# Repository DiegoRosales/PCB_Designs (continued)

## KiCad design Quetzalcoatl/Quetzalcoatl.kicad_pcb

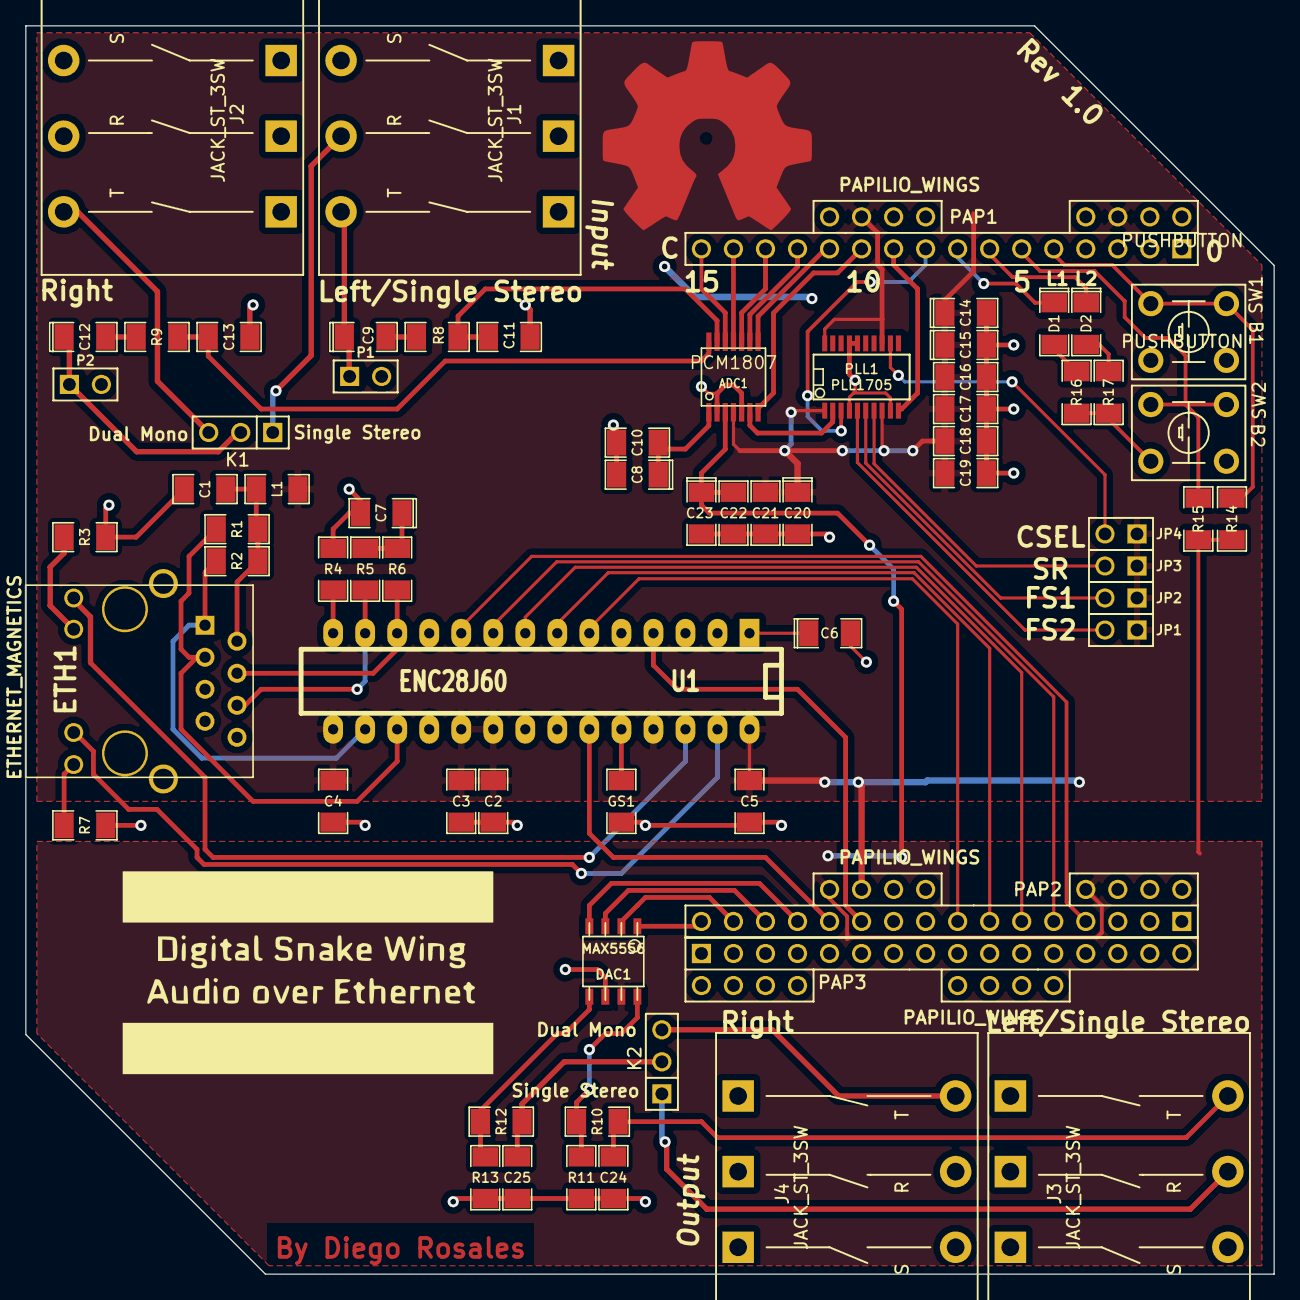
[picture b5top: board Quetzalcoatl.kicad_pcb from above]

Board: 2 copper layers, 99.0 x 99.0 mm, 68 parts (0 on the bottom side), 61 nets.

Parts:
ADC1: PCM1807; tssop-14
C1: 100nF; SM1206
C2, C3, C4, C5: 180nF; SM1206
C6, C8, C14, C15, C20, C23: 10uF; SM1206POL
C7: 10nF; SM1206POL
C9, C12: 1uF; SM1206POL
C10, C16, C17, C18, C19, C21, C22: 0.1uF; SM1206
C11, C13: 80nF; SM1206
C24, C25: 1.5nF; SM1206
D1, D2: LED; SM1206POL
DAC1: MAX5556; so-8
ETH1: ETHERNET_MAGNETICS; PRT-08534
GS1: GS2; SM1206
J1, J2, J3, J4: JACK_ST_3SW; Jack_6.35_Stereo_SW
JP1, JP2, JP3, JP4: JUMPER; PIN_ARRAY_2X1
K1, K2: CONN_3; PIN_ARRAY_3X1
L1: FERRITE_BEAD; SM1206
P1, P2: CONN_2; PIN_ARRAY_2X1
PAP1, PAP2, PAP3: PAPILIO_WINGS; Papilio_Wing
PLL1: PLL1705; SSOP20
R1, R2, R5, R6: 49.9, 1%; SM1206
R3, R7: 180R; SM1206
R4: 2.32k, 1%; SM1206
R8, R9: 100R; SM1206
R10, R12: 560R; SM1206
R11, R13: 100k; SM1206
R14, R15, R16, R17: 1k; SM1206
SW1, SW2: PUSHBUTTON; TactileSW_2
U1: ENC28J60; DIP-28__300_ELL

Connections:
+3.3V: ADC1.4, C2.1, C3.1, C4.1, C5.1, C14.1, C15.1, C16.1, C17.1, C18.1, C19.1, C20.1, C21.1, JP1.1, JP2.1, JP3.1, JP4.1, L1.1, PAP1.18, PAP1.22, PAP2.18, PLL1.1, PLL1.8, PLL1.13, PLL1.20, U1.15, U1.19, U1.20, U1.25, U1.28
+5V: ADC1.3, C22.1, C23.1, DAC1.7, PAP2.17, PAP2.21, R14.2, R15.2
/ADC/384fs: PAP1.9, PLL1.3
/ADC/ADC_CTRL_CK: ADC1.11, PAP1.15
/ADC/ADC_CTRL_DATA: ADC1.10, PAP1.14
/ADC/ADC_CTRL_SEL: ADC1.12, PAP1.16
/ADC/BCK: ADC1.8, PAP1.12
/ADC/CK27: PAP1.10, PLL1.10
/ADC/D_ADC: ADC1.9, PAP1.13
/ADC/LRCK: ADC1.7, PAP1.11
/ADC/Vin_L: ADC1.13, C11.1, R8.2
/ADC/Vin_R: ADC1.14, C13.1, R9.2
/DAC/LRCLK: DAC1.3, PAP2.14
/DAC/MCLK: DAC1.4, PAP2.13
/DAC/SCLK: DAC1.2, PAP2.15
/DAC/SDATA: DAC1.1, PAP2.16
/Ethernet/CK25: PAP2.12, U1.23
/Ethernet/CS: PAP2.5, U1.9
/Ethernet/ETH_INT: PAP2.11, U1.4
/Ethernet/LED_A: ETH1.11, U1.27
/Ethernet/LED_B: ETH1.9, U1.26
/Ethernet/MISO: PAP2.8, U1.6
/Ethernet/MOSI: PAP2.7, U1.7
/Ethernet/RESET: PAP2.4, U1.10
/Ethernet/SCK: PAP2.6, U1.8
/Misc/LED1: D1.1, PAP1.8
/Misc/LED2: D2.1, PAP1.7
/Misc/PB1: PAP1.5, R14.1, SW1.1, SW1.2
/Misc/PB2: PAP1.6, R15.1, SW2.1, SW2.2
GND: ADC1.2, ADC1.5, C1.2, C2.2, C3.2, C4.2, C5.2, C6.2, C7.2, C8.2, C10.2, C11.2, C13.2, C14.2, C15.2, C16.2, C17.2, C18.2, C19.2, C20.2, C21.2, C22.2, C23.2, C24.2, C25.2, DAC1.6, ETH1.8, GS1.2, J1.1, J1.3, J1.5, J1.6, J2.1, J2.3, J2.5, J2.6, J3.1, J3.3, J3.5, J3.6, J4.1, J4.3, J4.5, J4.6, P1.2, P2.2, PAP1.20, PAP1.24, PAP2.20, PAP2.24, PLL1.4, PLL1.9, PLL1.16, PLL1.17, R3.2, R4.1, R7.2, R11.1, R13.1, R16.2, R17.2, SW1.3, SW1.4, SW2.3, SW2.4, U1.2, U1.11, U1.18, U1.21, U1.22
unnamed: ETH1.10, R3.1
unnamed: ETH1.12, R7.1
unnamed: C7.1, R5.2, R6.2
unnamed: ETH1.6, R5.1, U1.13
unnamed: ETH1.1, R2.2, U1.16
unnamed: ETH1.3, R1.2, U1.17
unnamed: C6.1, U1.1
unnamed: R4.2, U1.14
unnamed: GS1.1, U1.24
unnamed: ETH1.4, R6.1, U1.12
unnamed: C1.1, ETH1.2, L1.2, R1.1, R2.1
unnamed: C9.1, J1.2, P1.1
unnamed: J1.4, K1.1
unnamed: J2.2, K1.3
unnamed: C12.1, K1.2, P2.1
unnamed: JP2.2, PLL1.6
unnamed: JP4.2, PLL1.12
unnamed: ADC1.1, C8.1, C10.1
unnamed: C9.2, R8.1
unnamed: C12.2, R9.1
unnamed: ADC1.6, PLL1.2
unnamed: JP1.2, PLL1.5
unnamed: JP3.2, PLL1.7
unnamed: J4.2, K2.3
unnamed: DAC1.8, R10.1, R11.2
unnamed: DAC1.5, R12.1, R13.2
unnamed: J3.4, K2.1
unnamed: C25.1, K2.2, R12.2
unnamed: C24.1, J3.2, R10.2
unnamed: D2.2, R17.1
unnamed: D1.2, R16.1

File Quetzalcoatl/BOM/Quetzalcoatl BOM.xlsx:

| Ref | Value | Qty per board | Total Qty | Part No. | Distributor | Dist. No. | Unit price (USD) | Cost
 | ADC1 | PCM1807 | 1 | 2 | PCM1807 | - | - | 0 | 0 |  | Boards | 2
 | C1 | 100nF | 1 | 2 | MC1206B104J500CT | Newark | 90W2887 | 0.29199999999999998 | 0.58399999999999996 |  | Total | 8.088000000000001
 | C10, C16, C17, C18, C19, C21, C22 | 0.1uF | 7 | 14 | CC1206KRX7R9BB104 | Newark | 68R4967 | 3.6999999999999998E-2 | 0.51800000000000002 |  | Total per board | 4.0440000000000005
 | C11, C13 | 80nF | 2 | 4 | C1206C183K5RACTU | Newark | 70K9301 | 4.9000000000000002E-2 | 0.19600000000000001
 | C2, C3, C4, C5 | 180nF | 4 | 8 | MC1206B184K250CT | Newark | 33R0653 | 7.2999999999999995E-2 | 0.58399999999999996
 | C24, C25 | 1.5nF | 2 | 4 | MC1206B152K102CT | Newark | 21T9895 | 0.03 | 0.12
 | C6, C8, C14, C15, C20, C23 | 10uF | 6 | 12 | 100R18Y106ZV4E | Newark | 82H2447 | 0.06 | 0.72
 | C7 | 10nF | 1 | 2 | 12061C103JAT2A | Newark | 96M1464 | 6.0999999999999999E-2 | 0.122
 | C9, C12 | 1uF | 2 | 4 | CC1206KKX7R7BB105 | Newark | 68R4957 | 0.06 | 0.24
 | DAC1 | MAX5556 | 1 | 2 | MAX5556 | - | - | 0 | 0
 | ETH1 | ETHERNET_MAGNETICS | 1 | 2 | PRT-08534 | Sparkfun |  | 1.95 | 3.9
 | GS1 | GS2 | 1 | 2 | - | - | - | 0 | 0
 | J1, J2, J3, J4 | JACK_ST_3SW | 4 | 8 | - | - | - | 0 | 0
 | JP1, JP2, JP3, JP4 | JUMPER | 4 | 8 | - | - | - | 0 | 0
 | L1 | FERRITE_BEAD | 1 | 2 | 2512061217Y0 | Newark | 32C8661 | 3.1E-2 | 6.2E-2
 | P1, P2 | CONN_2 | 2 | 4 | - | - | - | 0 | 0
 | PAP1, PAP2 | PAPILIO_WINGS | 2 | 4 | - | - | - | 0 | 0
 | PLL1 | PLL1705 | 1 | 2 | PLL1705 | - | - | 0 | 0
 | R1, R2, R5, R6 | 49.9R, 1% | 4 | 8 | CR1206-FX-49R9ELF | Newark | 02J2615 | 0.10100000000000001 | 0.80800000000000005
 | R10, R12 | 560R | 2 | 4 | CRCW1206560RFKEA | Newark | 42K5124 | 8.9999999999999993E-3 | 3.5999999999999997E-2
 | R11, R13 | 100k | 2 | 4 | MC0125W12061100K | Newark | 39K0873 | 2.1999999999999999E-2 | 8.7999999999999995E-2
 | R3, R7 | 180R | 2 | 4 | WCR1206-180RFI | Newark | 98K2692 | 1.0999999999999999E-2 | 4.3999999999999997E-2
 | R4 | 2.32k, 1% | 1 | 2 | CRCW12062K32FKEA | Newark | 53K2064 | 8.9999999999999993E-3 | 1.7999999999999999E-2
 | R8, R9 | 100R | 2 | 4 | MC0125W12065100R | Newark | 39K0992 | 1.2E-2 | 4.8000000000000001E-2
 | U1 | ENC28J60 | 1 | 2 | ENC28J60 | - | - | 0 | 0

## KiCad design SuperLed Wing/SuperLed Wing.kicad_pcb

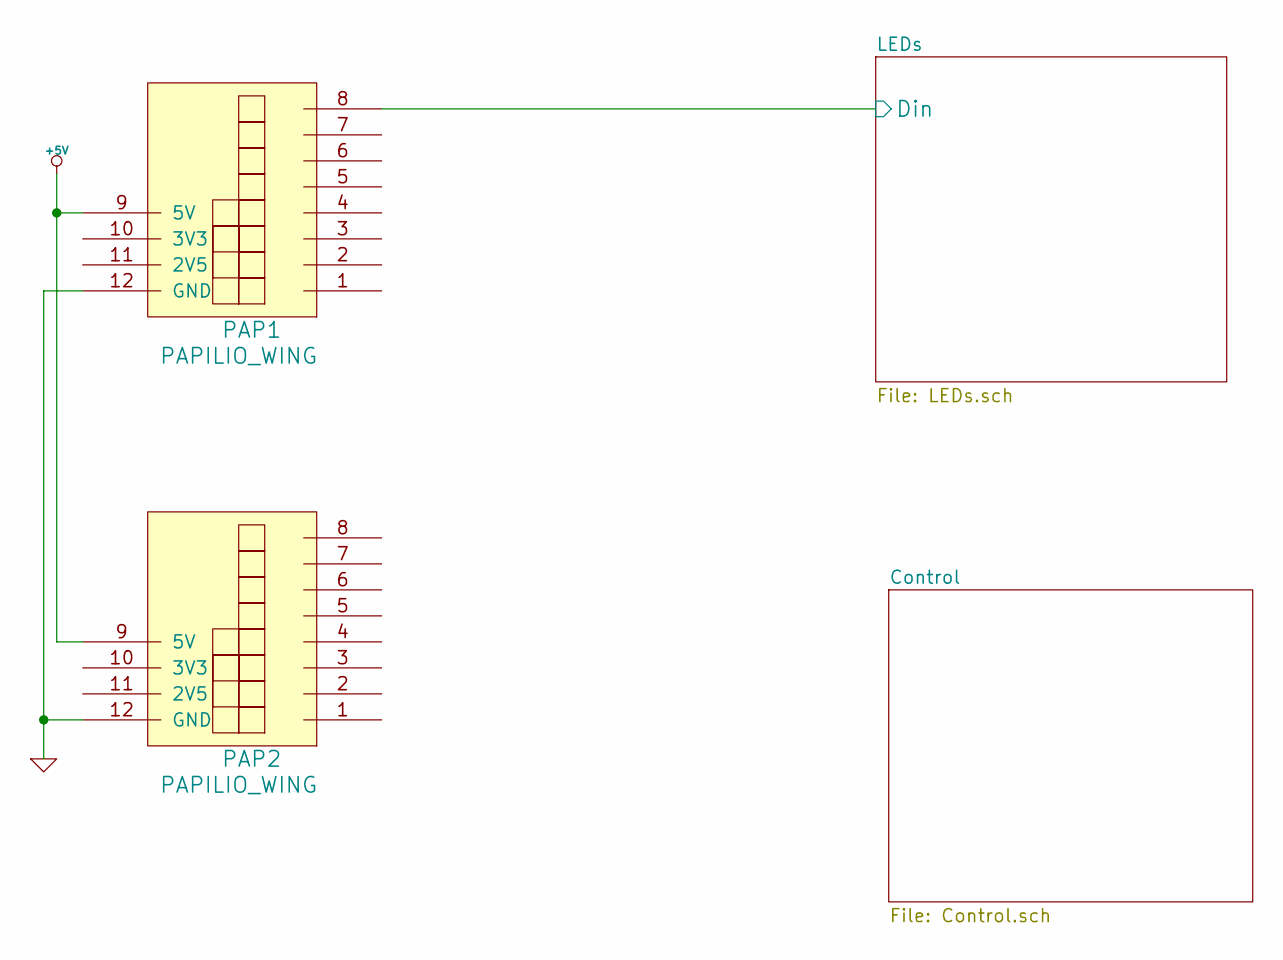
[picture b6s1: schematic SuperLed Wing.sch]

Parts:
PAP1, PAP2: PAPILIO_WING

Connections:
+5V: PAP1.9 (5V), PAP2.9 (5V)
/LEDs/Din: PAP1.8; also elsewhere on the board
GND: PAP1.12 (GND), PAP2.12 (GND); also elsewhere on the board

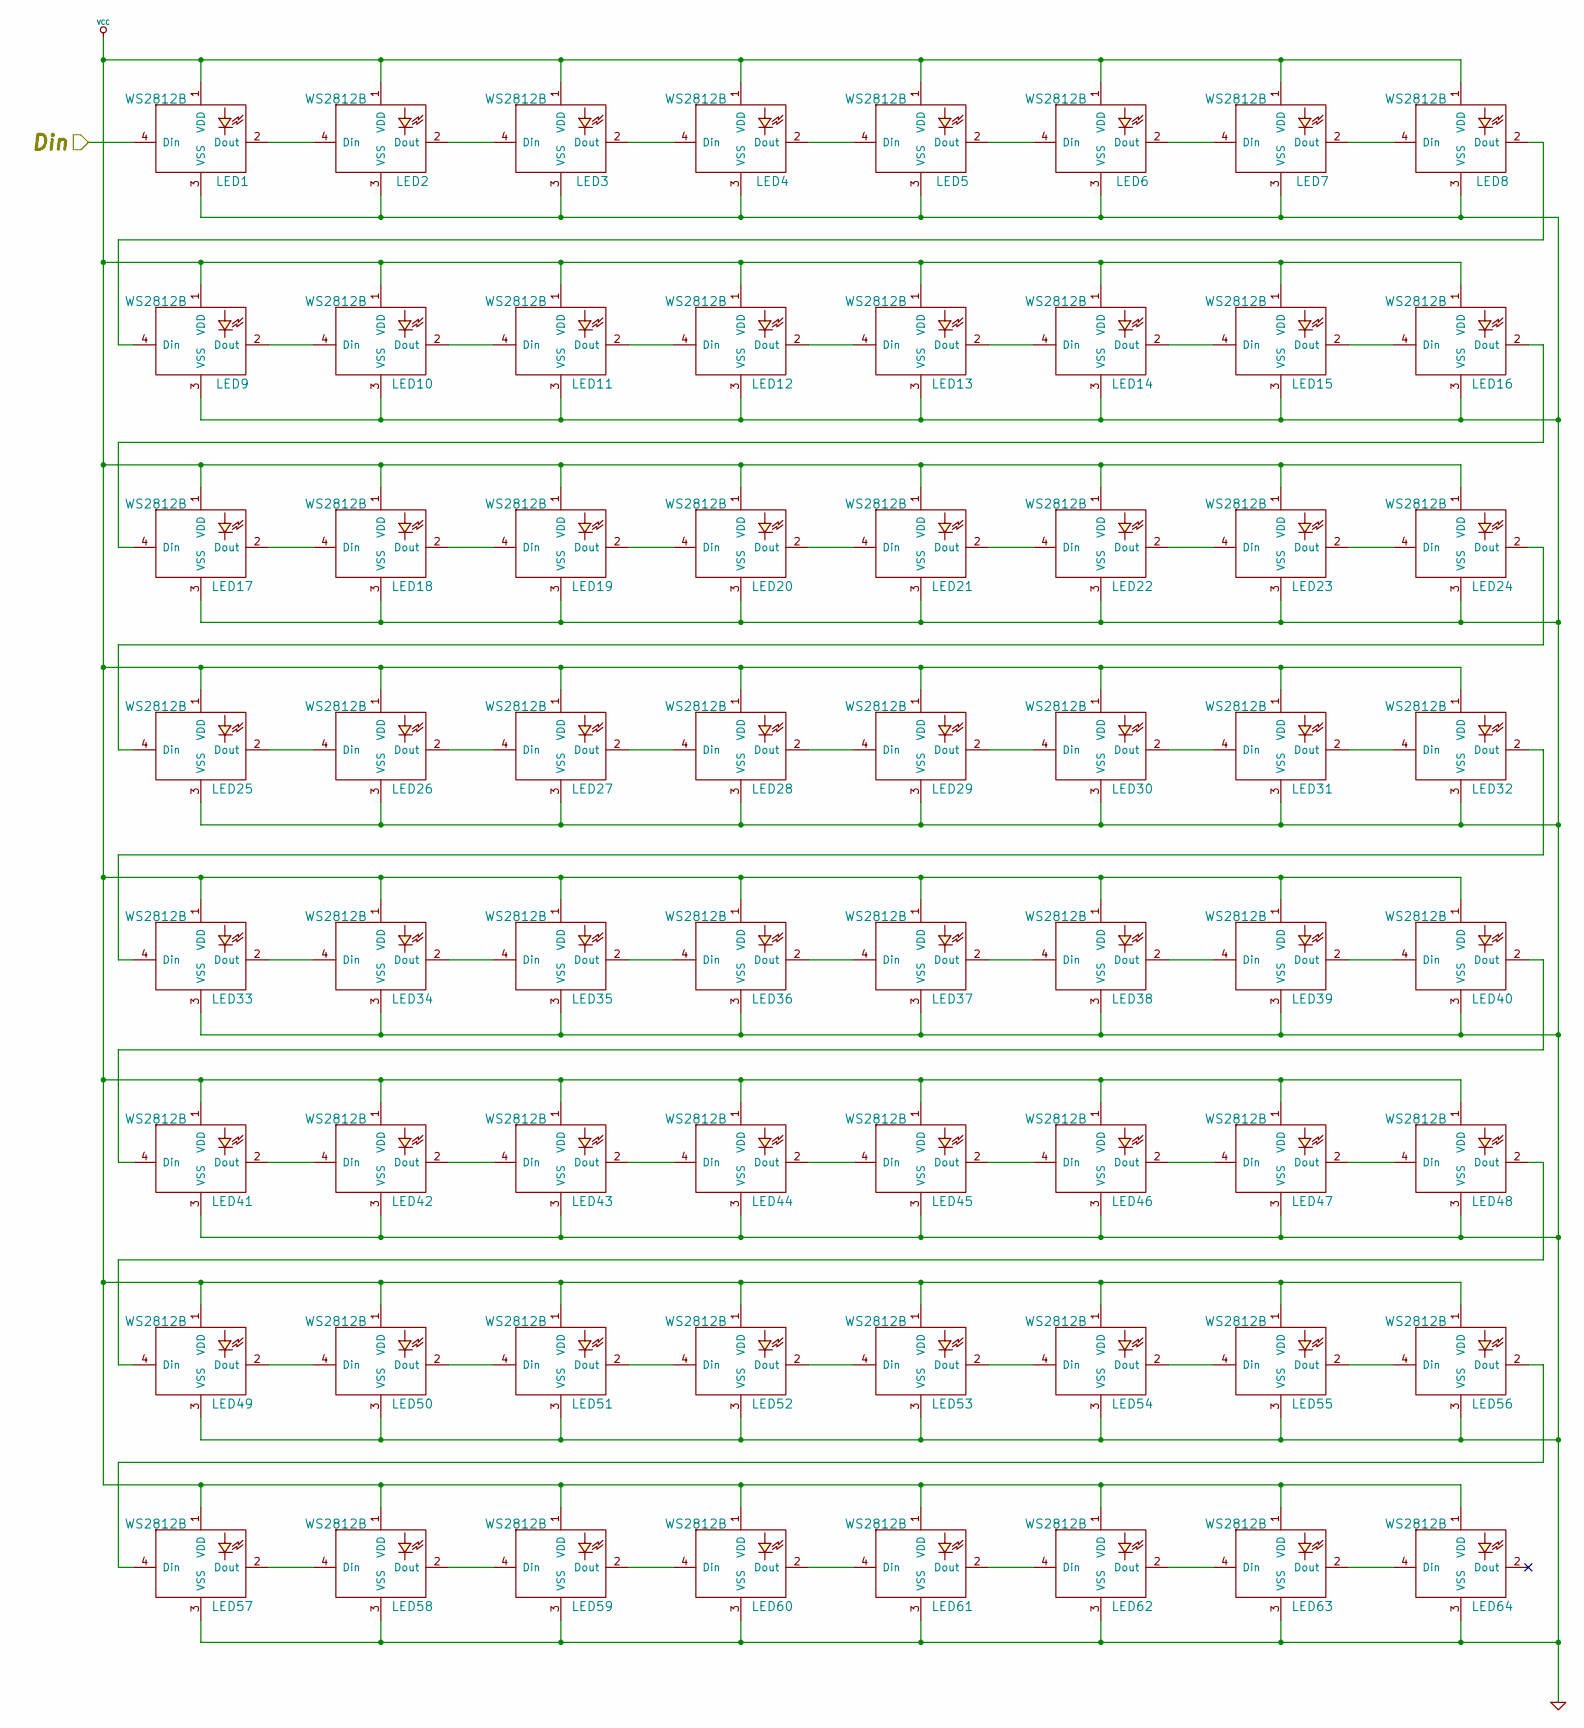
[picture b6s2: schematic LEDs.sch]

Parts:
LED1, LED2, LED3, LED4, LED5, LED6, LED7, LED8, LED9, LED10, LED11, LED12, LED13, LED14, LED15, LED16, LED17, LED18, LED19, LED20, LED21, LED22, LED23, LED24, LED25, LED26, LED27, LED28, LED29, LED30, LED31, LED32, LED33, LED34, LED35, LED36, LED37, LED38, LED39, LED40, LED41, LED42, LED43, LED44, LED45, LED46, LED47, LED48, LED49, LED50, LED51, LED52, LED53, LED54, LED55, LED56, LED57, LED58, LED59, LED60, LED61, LED62, LED63, LED64: WS2812B

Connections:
/LEDs/Din: LED1.4 (Din); also elsewhere on the board
GND: LED1.3 (VSS), LED2.3 (VSS), LED3.3 (VSS), LED4.3 (VSS), LED5.3 (VSS), LED6.3 (VSS), LED7.3 (VSS), LED8.3 (VSS), LED9.3 (VSS), LED10.3 (VSS), LED11.3 (VSS), LED12.3 (VSS), LED13.3 (VSS), LED14.3 (VSS), LED15.3 (VSS), LED16.3 (VSS), LED17.3 (VSS), LED18.3 (VSS), LED19.3 (VSS), LED20.3 (VSS), LED21.3 (VSS), LED22.3 (VSS), LED23.3 (VSS), LED24.3 (VSS), LED25.3 (VSS), LED26.3 (VSS), LED27.3 (VSS), LED28.3 (VSS), LED29.3 (VSS), LED30.3 (VSS), LED31.3 (VSS), LED32.3 (VSS), LED33.3 (VSS), LED34.3 (VSS), LED35.3 (VSS), LED36.3 (VSS), LED37.3 (VSS), LED38.3 (VSS), LED39.3 (VSS), LED40.3 (VSS), LED41.3 (VSS), LED42.3 (VSS), LED43.3 (VSS), LED44.3 (VSS), LED45.3 (VSS), LED46.3 (VSS), LED47.3 (VSS), LED48.3 (VSS), LED49.3 (VSS), LED50.3 (VSS), LED51.3 (VSS), LED52.3 (VSS), LED53.3 (VSS), LED54.3 (VSS), LED55.3 (VSS), LED56.3 (VSS), LED57.3 (VSS), LED58.3 (VSS), LED59.3 (VSS), LED60.3 (VSS), LED61.3 (VSS), LED62.3 (VSS), LED63.3 (VSS), LED64.3 (VSS); also elsewhere on the board
unnamed: LED33.2 (Dout), LED34.4 (Din)
unnamed: LED34.2 (Dout), LED35.4 (Din)
unnamed: LED35.2 (Dout), LED36.4 (Din)
unnamed: LED36.2 (Dout), LED37.4 (Din)
unnamed: LED37.2 (Dout), LED38.4 (Din)
unnamed: LED38.2 (Dout), LED39.4 (Din)
unnamed: LED39.2 (Dout), LED40.4 (Din)
unnamed: LED44.2 (Dout), LED45.4 (Din)
unnamed: LED41.2 (Dout), LED42.4 (Din)
unnamed: LED42.2 (Dout), LED43.4 (Din)
unnamed: LED43.2 (Dout), LED44.4 (Din)
unnamed: LED45.2 (Dout), LED46.4 (Din)
unnamed: LED46.2 (Dout), LED47.4 (Din)
unnamed: LED47.2 (Dout), LED48.4 (Din)
unnamed: LED17.2 (Dout), LED18.4 (Din)
unnamed: LED18.2 (Dout), LED19.4 (Din)
unnamed: LED19.2 (Dout), LED20.4 (Din)
unnamed: LED20.2 (Dout), LED21.4 (Din)
unnamed: LED21.2 (Dout), LED22.4 (Din)
unnamed: LED22.2 (Dout), LED23.4 (Din)
unnamed: LED14.2 (Dout), LED15.4 (Din)
unnamed: LED15.2 (Dout), LED16.4 (Din)
unnamed: LED23.2 (Dout), LED24.4 (Din)
unnamed: LED25.2 (Dout), LED26.4 (Din)
unnamed: LED26.2 (Dout), LED27.4 (Din)
unnamed: LED27.2 (Dout), LED28.4 (Din)
unnamed: LED28.2 (Dout), LED29.4 (Din)
unnamed: LED29.2 (Dout), LED30.4 (Din)
unnamed: LED30.2 (Dout), LED31.4 (Din)
unnamed: LED31.2 (Dout), LED32.4 (Din)
unnamed: LED8.2 (Dout), LED9.4 (Din)
unnamed: LED56.2 (Dout), LED57.4 (Din)
unnamed: LED40.2 (Dout), LED41.4 (Din)
unnamed: LED48.2 (Dout), LED49.4 (Din)
unnamed: LED16.2 (Dout), LED17.4 (Din)
unnamed: LED24.2 (Dout), LED25.4 (Din)
unnamed: LED32.2 (Dout), LED33.4 (Din)
unnamed: LED54.2 (Dout), LED55.4 (Din)
unnamed: LED49.2 (Dout), LED50.4 (Din)
unnamed: LED50.2 (Dout), LED51.4 (Din)
unnamed: LED51.2 (Dout), LED52.4 (Din)
unnamed: LED52.2 (Dout), LED53.4 (Din)
unnamed: LED53.2 (Dout), LED54.4 (Din)
unnamed: LED55.2 (Dout), LED56.4 (Din)
unnamed: LED57.2 (Dout), LED58.4 (Din)
unnamed: LED58.2 (Dout), LED59.4 (Din)
unnamed: LED59.2 (Dout), LED60.4 (Din)
unnamed: LED60.2 (Dout), LED61.4 (Din)
unnamed: LED61.2 (Dout), LED62.4 (Din)
unnamed: LED62.2 (Dout), LED63.4 (Din)
unnamed: LED63.2 (Dout), LED64.4 (Din)
unnamed: LED6.2 (Dout), LED7.4 (Din)
unnamed: LED7.2 (Dout), LED8.4 (Din)
unnamed: LED1.2 (Dout), LED2.4 (Din)
unnamed: LED2.2 (Dout), LED3.4 (Din)
unnamed: LED4.2 (Dout), LED5.4 (Din)
unnamed: LED3.2 (Dout), LED4.4 (Din)
unnamed: LED5.2 (Dout), LED6.4 (Din)
unnamed: LED9.2 (Dout), LED10.4 (Din)
unnamed: LED10.2 (Dout), LED11.4 (Din)
unnamed: LED11.2 (Dout), LED12.4 (Din)
unnamed: LED12.2 (Dout), LED13.4 (Din)
unnamed: LED13.2 (Dout), LED14.4 (Din)
VCC: LED1.1 (VDD), LED2.1 (VDD), LED3.1 (VDD), LED4.1 (VDD), LED5.1 (VDD), LED6.1 (VDD), LED7.1 (VDD), LED8.1 (VDD), LED9.1 (VDD), LED10.1 (VDD), LED11.1 (VDD), LED12.1 (VDD), LED13.1 (VDD), LED14.1 (VDD), LED15.1 (VDD), LED16.1 (VDD), LED17.1 (VDD), LED18.1 (VDD), LED19.1 (VDD), LED20.1 (VDD), LED21.1 (VDD), LED22.1 (VDD), LED23.1 (VDD), LED24.1 (VDD), LED25.1 (VDD), LED26.1 (VDD), LED27.1 (VDD), LED28.1 (VDD), LED29.1 (VDD), LED30.1 (VDD), LED31.1 (VDD), LED32.1 (VDD), LED33.1 (VDD), LED34.1 (VDD), LED35.1 (VDD), LED36.1 (VDD), LED37.1 (VDD), LED38.1 (VDD), LED39.1 (VDD), LED40.1 (VDD), LED41.1 (VDD), LED42.1 (VDD), LED43.1 (VDD), LED44.1 (VDD), LED45.1 (VDD), LED46.1 (VDD), LED47.1 (VDD), LED48.1 (VDD), LED49.1 (VDD), LED50.1 (VDD), LED51.1 (VDD), LED52.1 (VDD), LED53.1 (VDD), LED54.1 (VDD), LED55.1 (VDD), LED56.1 (VDD), LED57.1 (VDD), LED58.1 (VDD), LED59.1 (VDD), LED60.1 (VDD), LED61.1 (VDD), LED62.1 (VDD), LED63.1 (VDD), LED64.1 (VDD)

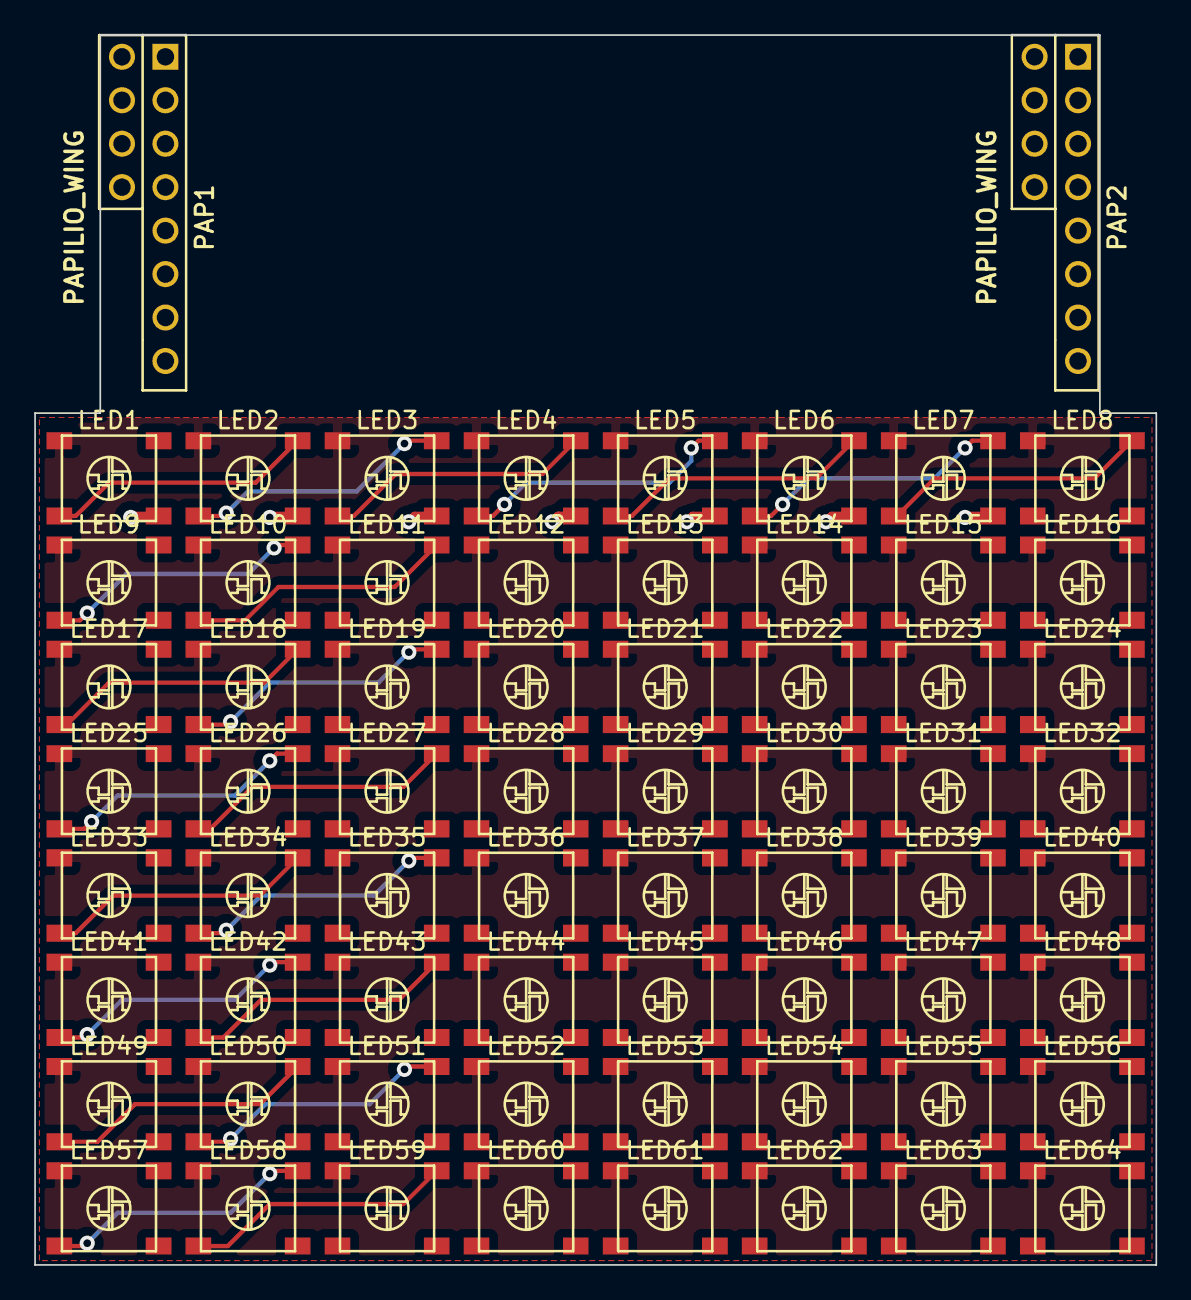
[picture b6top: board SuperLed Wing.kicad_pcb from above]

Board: 2 copper layers, 65.5 x 71.9 mm, 66 parts (0 on the bottom side), 67 nets.
